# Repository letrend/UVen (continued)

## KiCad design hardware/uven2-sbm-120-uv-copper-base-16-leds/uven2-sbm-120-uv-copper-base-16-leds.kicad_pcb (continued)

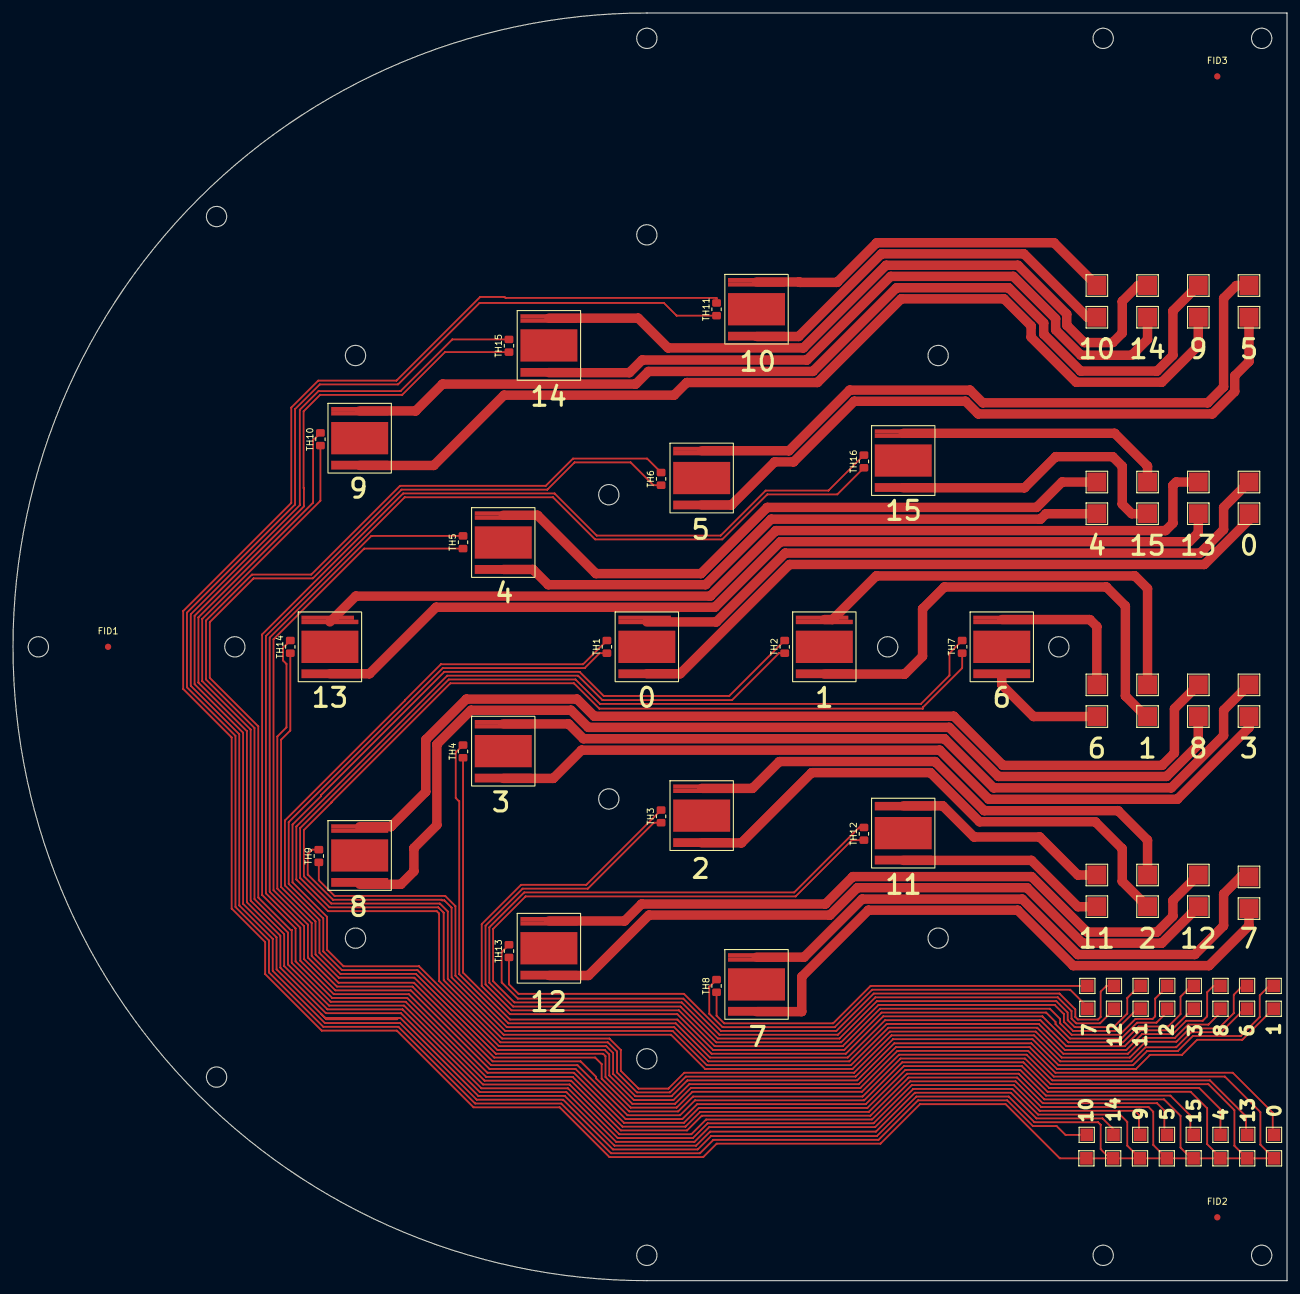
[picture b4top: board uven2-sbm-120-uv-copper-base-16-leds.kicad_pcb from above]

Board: 2 copper layers, 201.0 x 200.0 mm, 119 parts (0 on the bottom side), 49 nets.

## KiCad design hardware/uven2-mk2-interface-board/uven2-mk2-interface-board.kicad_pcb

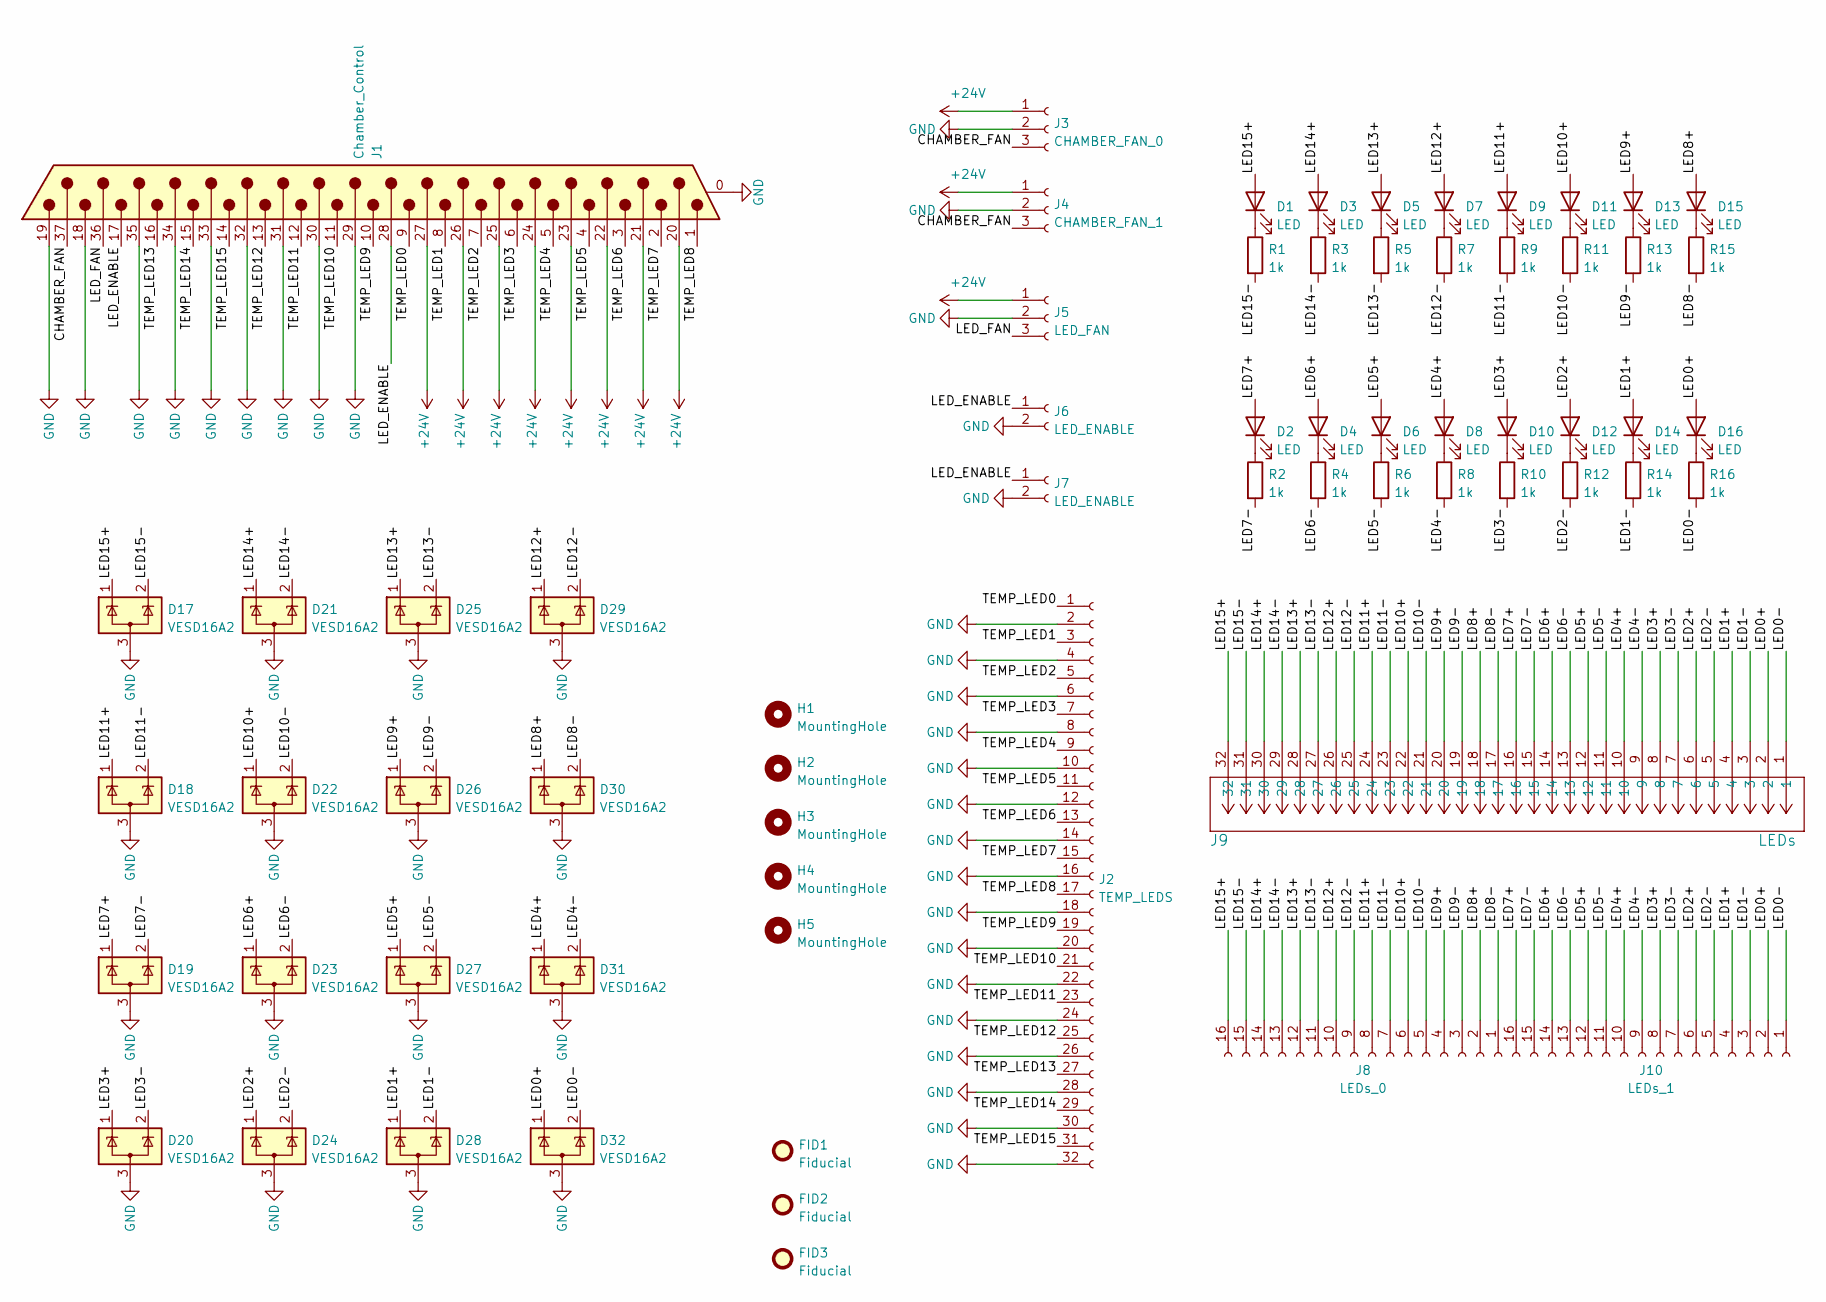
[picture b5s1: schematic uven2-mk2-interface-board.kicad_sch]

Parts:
D1, D2, D3, D4, D5, D6, D7, D8, D9, D10, D11, D12, D13, D14, D15, D16: LED; LED_0805_2012Metric_Pad1.15x1.40mm_HandSolder
D17, D18, D19, D20, D21, D22, D23, D24, D25, D26, D27, D28, D29, D30, D31, D32: VESD16A2; SOT-23
FID1, FID2, FID3: Fiducial; Fiducial_1mm_Dia_2.54mm_Outer_CopperTop
H1, H2, H3, H4, H5: MountingHole; MountingHole_3.2mm_M3
J1: Chamber_Control; DSUB-37_Female_Horizontal_P2.77x2.84mm_EdgePinOffset7.70mm_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
J2: TEMP_LEDS; PinHeader_2x16_P2.54mm_Vertical
J3: CHAMBER_FAN_0; PinHeader_1x03_P2.54mm_Vertical
J4: CHAMBER_FAN_1; PinHeader_1x03_P2.54mm_Vertical
J5: LED_FAN; PinHeader_1x03_P2.54mm_Vertical
J6, J7: LED_ENABLE; PinHeader_1x02_P2.54mm_Vertical
J8: LEDs_0; PinHeader_1x16_P2.54mm_Vertical
J9: LEDs; CONN_713-1436&slash_037-000_WAG
J10: LEDs_1; PinHeader_1x16_P2.54mm_Vertical
R1, R2, R3, R4, R5, R6, R7, R8, R9, R10, R11, R12, R13, R14, R15, R16: 1k; R_0603_1608Metric_Pad0.98x0.95mm_HandSolder

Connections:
+24V: J1.20, J1.21, J1.22, J1.23, J1.24, J1.25, J1.26, J1.27, J3.1, J4.1, J5.1
/CHAMBER_FAN: J1.37, J3.3, J4.3
/LED0+: D16.2 (A), D32.1 (K), J9.2, J10.2
/LED0-: D32.2 (K), J9.1, J10.1, R16.2
/LED1+: D14.2 (A), D28.1 (K), J9.4, J10.4
/LED1-: D28.2 (K), J9.3, J10.3, R14.2
/LED2+: D12.2 (A), D24.1 (K), J9.6, J10.6
/LED2-: D24.2 (K), J9.5, J10.5, R12.2
/LED3+: D10.2 (A), D20.1 (K), J9.8, J10.8
/LED3-: D20.2 (K), J9.7, J10.7, R10.2
/LED4+: D8.2 (A), D31.1 (K), J9.10, J10.10
/LED4-: D31.2 (K), J9.9, J10.9, R8.2
/LED5+: D6.2 (A), D27.1 (K), J9.12, J10.12
/LED5-: D27.2 (K), J9.11, J10.11, R6.2
/LED6+: D4.2 (A), D23.1 (K), J9.14, J10.14
/LED6-: D23.2 (K), J9.13, J10.13, R4.2
/LED7+: D2.2 (A), D19.1 (K), J9.16, J10.16
/LED7-: D19.2 (K), J9.15, J10.15, R2.2
/LED8+: D15.2 (A), D30.1 (K), J8.2, J9.18
/LED8-: D30.2 (K), J8.1, J9.17, R15.2
/LED9+: D13.2 (A), D26.1 (K), J8.4, J9.20
/LED9-: D26.2 (K), J8.3, J9.19, R13.2
/LED10+: D11.2 (A), D22.1 (K), J8.6, J9.22
/LED10-: D22.2 (K), J8.5, J9.21, R11.2
/LED11+: D9.2 (A), D18.1 (K), J8.8, J9.24
/LED11-: D18.2 (K), J8.7, J9.23, R9.2
/LED12+: D7.2 (A), D29.1 (K), J8.10, J9.26
/LED12-: D29.2 (K), J8.9, J9.25, R7.2
/LED13+: D5.2 (A), D25.1 (K), J8.12, J9.28
/LED13-: D25.2 (K), J8.11, J9.27, R5.2
/LED14+: D3.2 (A), D21.1 (K), J8.14, J9.30
/LED14-: D21.2 (K), J8.13, J9.29, R3.2
/LED15+: D1.2 (A), D17.1 (K), J8.16, J9.32
/LED15-: D17.2 (K), J8.15, J9.31, R1.2
/LED_ENABLE: J1.17, J1.28, J6.1, J7.1
/LED_FAN: J1.36, J5.3
/TEMP_LED0: J1.9, J2.1
/TEMP_LED1: J1.8, J2.3
/TEMP_LED2: J1.7, J2.5
/TEMP_LED3: J1.6, J2.7
/TEMP_LED4: J1.5, J2.9
/TEMP_LED5: J1.4, J2.11
/TEMP_LED6: J1.3, J2.13
/TEMP_LED7: J1.2, J2.15
/TEMP_LED8: J1.1, J2.17
/TEMP_LED9: J1.10, J2.19
/TEMP_LED10: J1.11, J2.21
/TEMP_LED11: J1.12, J2.23
/TEMP_LED12: J1.13, J2.25
/TEMP_LED13: J1.16, J2.27
/TEMP_LED14: J1.15, J2.29
/TEMP_LED15: J1.14, J2.31
GND: D17.3 (A), D18.3 (A), D19.3 (A), D20.3 (A), D21.3 (A), D22.3 (A), D23.3 (A), D24.3 (A), D25.3 (A), D26.3 (A), D27.3 (A), D28.3 (A), D29.3 (A), D30.3 (A), D31.3 (A), D32.3 (A), J1.0 (PAD), J1.18, J1.19, J1.29, J1.30, J1.31, J1.32, J1.33, J1.34, J1.35, J2.2, J2.4, J2.6, J2.8, J2.10, J2.12, J2.14, J2.16, J2.18, J2.20, J2.22, J2.24, J2.26, J2.28, J2.30, J2.32, J3.2, J4.2, J5.2, J6.2, J7.2
unnamed: D1.1 (K), R1.1
unnamed: D2.1 (K), R2.1
unnamed: D3.1 (K), R3.1
unnamed: D4.1 (K), R4.1
unnamed: D5.1 (K), R5.1
unnamed: D6.1 (K), R6.1
unnamed: D7.1 (K), R7.1
unnamed: D8.1 (K), R8.1
unnamed: D9.1 (K), R9.1
unnamed: D10.1 (K), R10.1
unnamed: D11.1 (K), R11.1
unnamed: D12.1 (K), R12.1
unnamed: D13.1 (K), R13.1
unnamed: D14.1 (K), R14.1
unnamed: D15.1 (K), R15.1
unnamed: D16.1 (K), R16.1

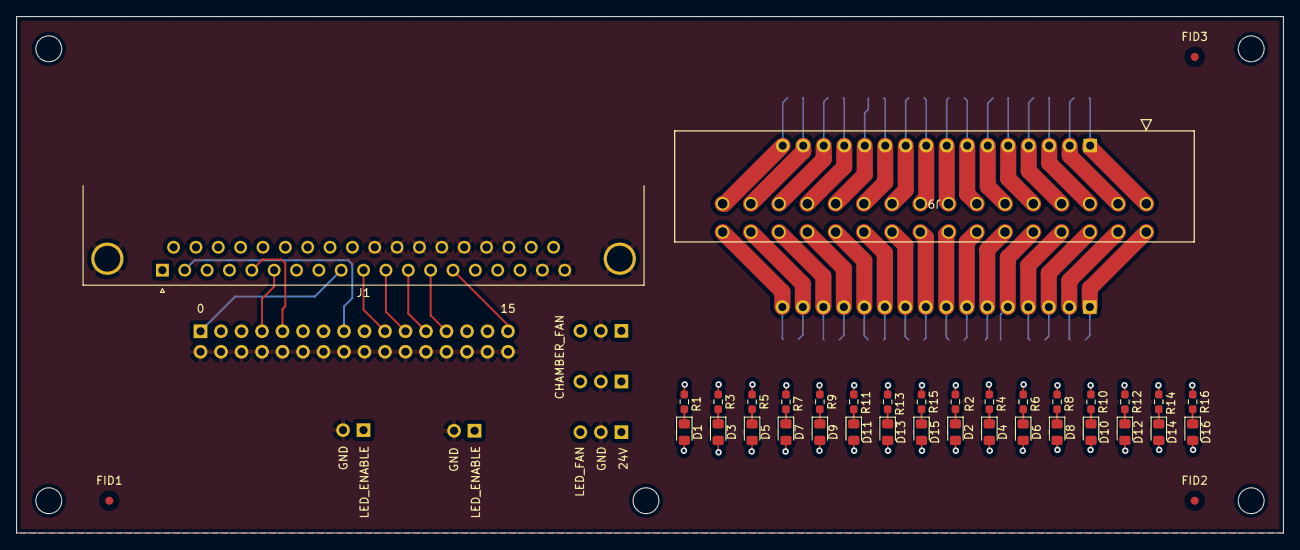
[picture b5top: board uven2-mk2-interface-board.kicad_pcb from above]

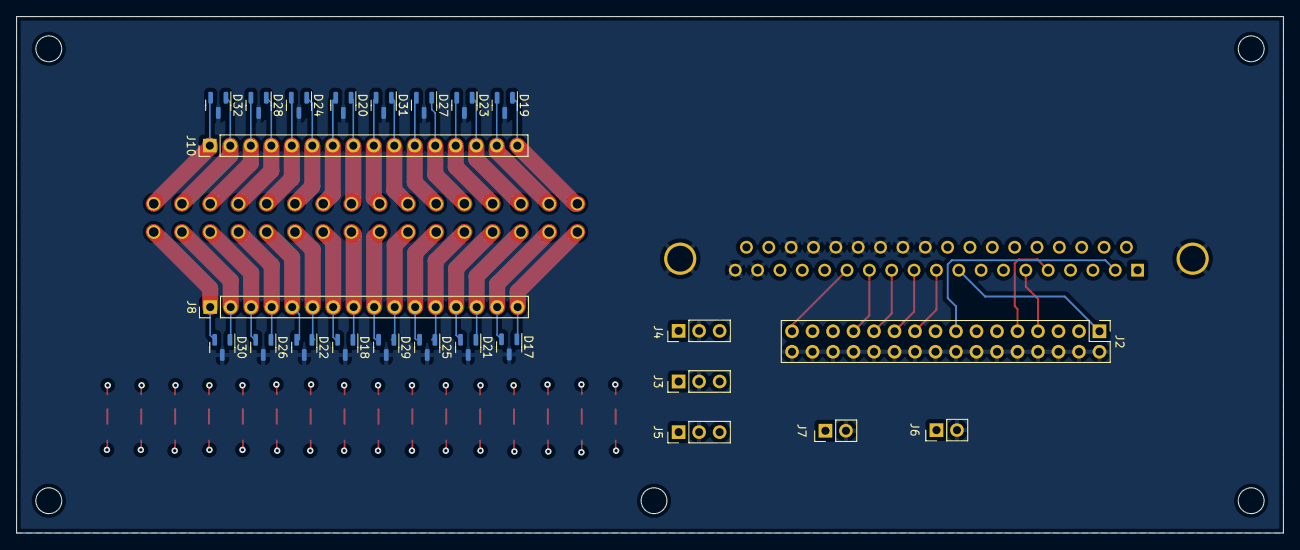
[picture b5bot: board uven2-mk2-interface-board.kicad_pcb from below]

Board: 4 copper layers, 157.0 x 64.0 mm, 66 parts (24 on the bottom side), 69 nets.

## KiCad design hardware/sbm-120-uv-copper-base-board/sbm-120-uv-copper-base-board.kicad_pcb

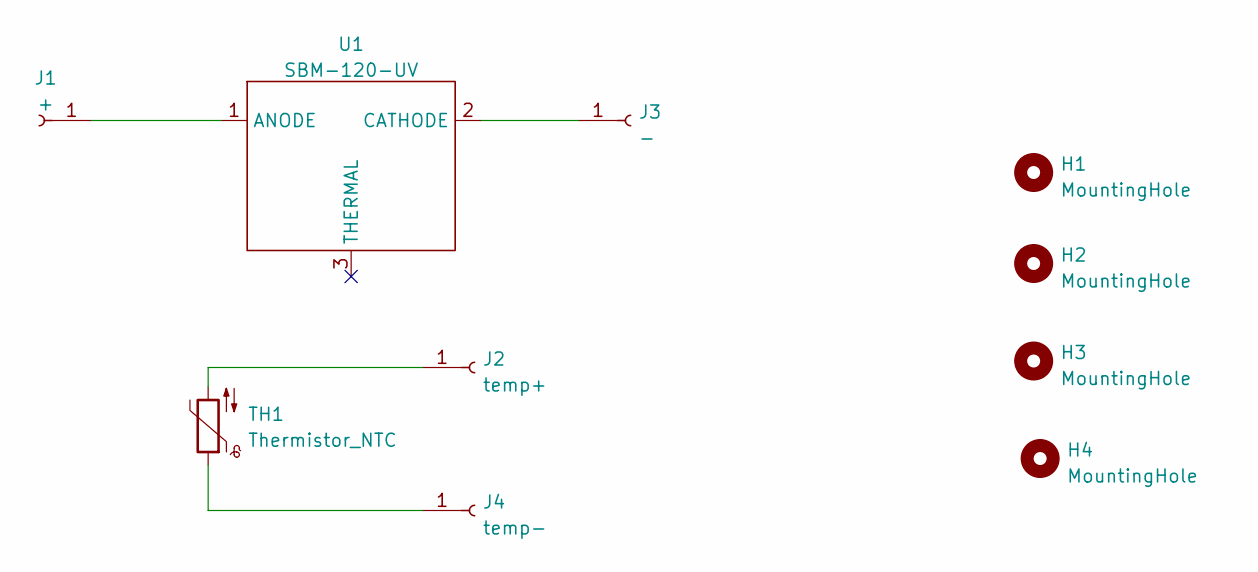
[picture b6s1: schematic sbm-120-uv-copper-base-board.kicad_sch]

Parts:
H1, H2, H3, H4: MountingHole; MountingHole_3.2mm_M3
J1: +; TestPoint_Pad_3.0x3.0mm
J2: temp+; TestPoint_Pad_1.5x1.5mm
J3: -; TestPoint_Pad_3.0x3.0mm
J4: temp-; TestPoint_Pad_1.5x1.5mm
TH1: Thermistor_NTC; R_0805_2012Metric_Pad1.20x1.40mm_HandSolder
U1: SBM-120-UV

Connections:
unnamed: J1.1, U1.1 (ANODE)
unnamed: J3.1, U1.2 (CATHODE)
unnamed: J4.1, TH1.1
unnamed: J2.1, TH1.2

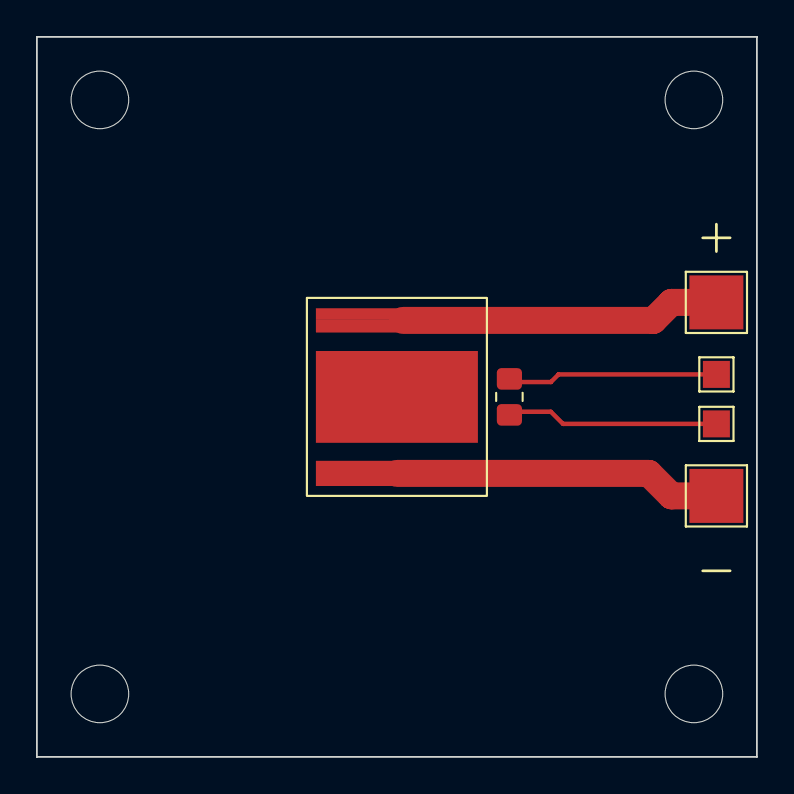
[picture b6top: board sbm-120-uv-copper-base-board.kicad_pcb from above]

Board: 2 copper layers, 40.0 x 40.0 mm, 10 parts (0 on the bottom side), 4 nets.

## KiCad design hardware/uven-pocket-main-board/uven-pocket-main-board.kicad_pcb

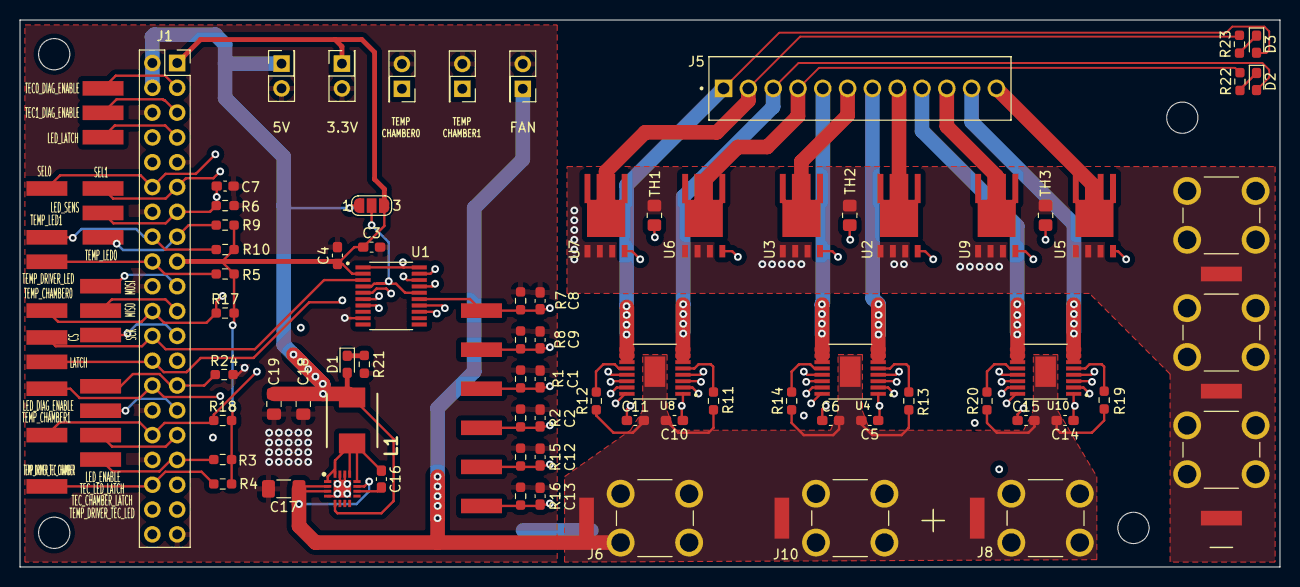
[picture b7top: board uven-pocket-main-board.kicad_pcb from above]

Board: 4 copper layers, 129.0 x 56.0 mm, 113 parts (0 on the bottom side), 57 nets.

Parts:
11111: TS30012-M050QFNR; QFN50P300X300X100-17N-D
C1, C2, C3, C8, C9, C12, C13: 100n; C_0603_1608Metric_Pad1.08x0.95mm_HandSolder
C4: 10uF; C_0603_1608Metric_Pad1.08x0.95mm_HandSolder
C5, C10, C14: 220n; C_0603_1608Metric_Pad1.08x0.95mm_HandSolder
C6, C11, C15: 4.7u; C_0603_1608Metric_Pad1.08x0.95mm_HandSolder
C7: 10n; C_0603_1608Metric_Pad1.08x0.95mm_HandSolder
C16: 0.022uF 10V; C_0603_1608Metric_Pad1.08x0.95mm_HandSolder
C17: 10uF 35V; C_1206_3216Metric_Pad1.33x1.80mm_HandSolder
C18, C19: 22uF; C_0805_2012Metric_Pad1.18x1.45mm_HandSolder
D1, D2, D3: LED; LED_0603_1608Metric_Pad1.05x0.95mm_HandSolder
H1, H2, H3, H4: MountingHole; MountingHole_3.2mm_M3
J1: Raspberry_Pi_2_3; PinSocket_2x20_P2.54mm_Vertical
J2: FAN; PinSocket_2x01_P2.54mm_Vertical
J3: TEMP_CHAMBER1; PinSocket_2x01_P2.54mm_Vertical
J4: TEMP_CHAMBER0; PinSocket_2x01_P2.54mm_Vertical
J5: 1-282834-2; TE_1-282834-2
J6, J8, J10: VDrive; KEYSTONE_7767
J7, J9, J11: GND; KEYSTONE_7767
J12: 3.3V; PinSocket_2x01_P2.54mm_Vertical
J13: 5V; PinSocket_2x01_P2.54mm_Vertical
JP1: Vref_select; SolderJumper-3_P1.3mm_Open_RoundedPad1.0x1.5mm_NumberLabels
L1: IHLP2020CZER4R7MA1; INDPM5552X300N
R1, R2, R6, R7, R8, R15, R16: 1k; R_0603_1608Metric_Pad0.98x0.95mm_HandSolder
R3, R4, R5, R9, R10, R11, R12, R13, R14, R17, R18, R19, R20, R22, R23, R24: 10k; R_0603_1608Metric_Pad0.98x0.95mm_HandSolder
R21: 1K; R_0603_1608Metric_Pad0.98x0.95mm_HandSolder
TH1, TH2, TH3: Thermistor_NTC; R_0805_2012Metric_Pad1.20x1.40mm_HandSolder
TP1: GATE_LED0; TP420X150
TP2: GATE_LED1; TP420X150
TP3: GATE_TEC0; TP420X150
TP4: GATE_TEC1; TP420X150
TP5: GATE_TEC2; TP420X150
TP6: GATE_TEC3; TP420X150
TP7, TP9, TP11: VDrive; TP420X150
TP8, TP10, TP12: GND; TP420X150
TP13: TEMP_DRIVER_LED; TP420X150
TP14: TEMP_CHAMBER0; TP420X150
TP15: LED_SENS; TP420X150
TP16: TEMP_DRIVER_TEC_CHAMBER; TP420X150
TP17: TEMP_LED0; TP420X150
TP18: TEMP_LED1; TP420X150
TP19: SEL1; TP420X150
TP20: SEL0; TP420X150
TP21: LATCH; TP420X150
TP22: CS; TP420X150
TP23: MISO; TP420X150
TP24: MOSI; TP420X150
TP25: SCK; TP420X150
TP26: LED_ENABLE; TP420X150
TP27: LED_DIAG_ENABLE; TP420X150
TP28: TEC0_DIAG_ENABLE; TP420X150
TP29: TEC1_DIAG_ENABLE; TP420X150
TP30: LED_LATCH; TP420X150
TP31: TEC_LED_LATCH; TP420X150
TP32: TEC_CHAMBER_LATCH; TP420X150
TP33: TEMP_CHAMBER1; TP420X150
TP34: TEMP_DRIVER_TEC_LED; TP420X150
U1: MCP48FEB28T-20E/ST; SOP65P640X120-20N
U2, U3, U5, U6, U7, U9: SIDR392DP-T1-GE3; PowerPAK SO-8DC
U4, U8, U10: TPS2HB50BQPWPRQ1; SOP65P640X120-17N

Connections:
+3.3V: C3.1, C4.1, J1.1 (3V3), J1.17 (3V3), J12.1, JP1.3 (B), R3.2, R4.2, R5.2, R9.2, R10.2, R17.2, R18.2, U1.2 (VDD)
+5V: 11111.5 (FB), C18.2, C19.2, D1.2 (A), J1.2 (5V), J1.4 (5V), J13.1, JP1.1 (A), L1.2
/CS: J1.24 (~CE0/GPIO8), TP22.1, U1.3 (CS)
/GATE_LED0: C9.2, R8.2, TP1.1, U1.5 (VOUTO), U6.4 (G)
/GATE_LED1: C8.2, R7.2, TP2.1, U1.15 (VOUT1), U7.4 (G)
/GATE_TEC0: C2.2, R2.2, TP3.1, U1.6 (VOUT2), U2.4 (G)
/GATE_TEC1: C1.2, R1.2, TP4.1, U1.14 (VOUT3), U3.4 (G)
/GATE_TEC2: C13.2, R16.2, TP5.1, U1.7 (VOUT4), U5.4 (G)
/GATE_TEC3: C12.2, R15.2, TP6.1, U1.13 (VOUT5), U9.4 (G)
/LATCH: J1.26 (~CE1/GPIO7), TP21.1, U1.1 (LAT1), U1.20 (LAT0)
/LED0+: D2.2 (A), J5.3, U8.6 (VOUT1), U8.7 (VOUT1), U8.8 (VOUT1)
/LED0-: J5.4, R22.2, U6.5 (D)
/LED1+: D3.2 (A), J5.1, U8.9 (VOUT2), U8.10 (VOUT2), U8.11 (VOUT2)
/LED1-: J5.2, R23.2, U7.5 (D)
/LED_DIAG_ENABLE: J1.28 (ID_SC/GPIO1), TP27.1, U8.16 (DIA_EN)
/LED_ENABLE: J1.27 (ID_SD/GPIO0), R24.2, TP26.1, U8.4 (EN1), U8.13 (EN2)
/LED_LATCH: J1.7 (GCLK0/GPIO4), TP30.1, U8.3 (LATCH)
/LED_SENS: C7.1, J1.13 (GPIO27), R6.1, TP15.1, U4.2 (SNS), U8.2 (SNS), U10.2 (SNS)
/SEL0: J1.12 (GPIO18/PWM0), TP20.1, U4.14 (SEL1), U8.14 (SEL1), U10.14 (SEL1)
/SEL1: J1.11 (GPIO17), TP19.1, U4.15 (SEL2), U8.15 (SEL2), U10.15 (SEL2)
/SPI_MISO: J1.21 (MISO0/GPIO9), TP23.1, U1.17 (SDO)
/SPI_MOSI: J1.19 (MOSI0/GPIO10), TP24.1, U1.19 (SDI)
/SPI_SCK: J1.23 (SCLK0/GPIO11), TP25.1, U1.18 (SCK)
/TEC0+: J5.7, U4.6 (VOUT1), U4.7 (VOUT1), U4.8 (VOUT1)
/TEC0-: J5.8, U2.5 (D)
/TEC0_DIAG_ENABLE: J1.3 (SDA/GPIO2), TP28.1, U4.16 (DIA_EN)
/TEC1+: J5.5, U4.9 (VOUT2), U4.10 (VOUT2), U4.11 (VOUT2)
/TEC1-: J5.6, U3.5 (D)
/TEC1_DIAG_ENABLE: J1.5 (SCL/GPIO3), TP29.1, U10.16 (DIA_EN)
/TEC2+: J5.11, U10.6 (VOUT1), U10.7 (VOUT1), U10.8 (VOUT1)
/TEC2-: J5.12, U5.5 (D)
/TEC3+: J5.9, U10.9 (VOUT2), U10.10 (VOUT2), U10.11 (VOUT2)
/TEC3-: J5.10, U9.5 (D)
/TEC_CHAMBER_LATCH: J1.31 (GCLK2/GPIO6), TP32.1, U10.3 (LATCH)
/TEC_ENABLE: U4.4 (EN1), U4.13 (EN2), U10.4 (EN1), U10.13 (EN2)
/TEC_LED_LATCH: J1.29 (GCLK1/GPIO5), TP31.1, U4.3 (LATCH)
/TEMP_CHAMBER0: J1.22 (GPIO25), J4.1, R17.1, TP14.1
/TEMP_CHAMBER1: J1.32 (PWM0/GPIO12), J3.1, R18.1, TP33.1
/TEMP_DRIVER_LED: J1.18 (GPIO24), R5.1, TH1.2, TP13.1
/TEMP_DRIVER_TEC_CHAMBER: J1.36 (GPIO16), R4.1, TH3.2, TP16.1
/TEMP_DRIVER_TEC_LED: J1.33 (PWM1/GPIO13), R3.1, TH2.2, TP34.1
/TEMP_LED0: J1.15 (GPIO22), R9.1, TP17.1
/TEMP_LED1: J1.16 (GPIO23), R10.1, TP18.1
GND: 11111.4 (GND), 11111.14 (PGND_1), 11111.15 (PGND_2), 11111.17 (EP), C1.1, C2.1, C3.2, C4.2, C5.1, C6.1, C7.2, C8.1, C9.1, C10.1, C11.1, C12.1, C13.1, C14.1, C15.1, C17.2, C18.1, C19.1, J1.6 (GND), J1.9 (GND), J1.14 (GND), J1.20 (GND), J1.25 (GND), J1.30 (GND), J1.34 (GND), J1.39 (GND), J2.2, J3.2, J4.2, J7.1, J7.2, J7.3, J7.4, J9.1, J9.2, J9.3, J9.4, J11.1, J11.2, J11.3, J11.4, J12.2, J13.2, R1.1, R2.1, R6.2, R7.1, R8.1, R15.1, R16.1, R21.2, R24.1, TH1.1, TH2.1, TH3.1, TP8.1, TP10.1, TP12.1, U1.9 (VSS), U2.1 (S), U2.2 (S), U2.3 (S), U3.1 (S), U3.2 (S), U3.3 (S), U4.1 (GND), U5.1 (S), U5.2 (S), U5.3 (S), U6.1 (S), U6.2 (S), U6.3 (S), U7.1 (S), U7.2 (S), U7.3 (S), U8.1 (GND), U9.1 (S), U9.2 (S), U9.3 (S), U10.1 (GND)
unnamed: 11111.1 (VSW_1), 11111.12 (VSW_2), 11111.13 (VSW_3), 11111.16 (VSW_4), C16.1, L1.1
unnamed: 11111.10 (BST), C16.2
unnamed: D1.1 (K), R21.1
unnamed: D2.1 (K), R22.1
unnamed: D3.1 (K), R23.1
unnamed: JP1.2 (C), U1.4 (VREF0), U1.16 (VREF1)
unnamed: R11.2, U8.5 (ILIM1)
unnamed: R12.2, U8.12 (ILIM2)
unnamed: R13.2, U4.5 (ILIM1)
unnamed: R14.2, U4.12 (ILIM2)
unnamed: R19.2, U10.5 (ILIM1)
unnamed: R20.2, U10.12 (ILIM2)
Vdrive: 11111.2 (VCC_1), 11111.3 (VCC_2), 11111.11 (VCC_3), C5.2, C6.2, C10.2, C11.2, C14.2, C15.2, C17.1, J2.1, J6.1, J6.2, J6.3, J6.4, J8.1, J8.2, J8.3, J8.4, J10.1, J10.2, J10.3, J10.4, R11.1, R12.1, R13.1, R14.1, R19.1, R20.1, TP7.1, TP9.1, TP11.1, U4.17 (VBB), U8.17 (VBB), U10.17 (VBB)

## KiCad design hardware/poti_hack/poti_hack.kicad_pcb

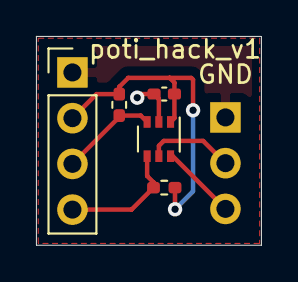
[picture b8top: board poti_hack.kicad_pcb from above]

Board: 2 copper layers, 12.5 x 11.6 mm, 6 parts (1 on the bottom side), 6 nets.

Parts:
C1: 100nF; C_0402_1005Metric_Pad0.74x0.62mm_HandSolder
J1: POTI_i2c; PinHeader_1x04_P2.54mm_Vertical
J2: POTI; PinHeader_1x03_P2.54mm_Vertical
R1, R2: 10k; R_0402_1005Metric_Pad0.72x0.64mm_HandSolder
U1: MCP4018-xxxxLT; SOT-363_SC-70-6

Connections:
+3V3: C1.1, J1.2, R1.1, R2.1, U1.1
GND: C1.2, J1.1, J2.1, U1.2
unnamed: J1.3, R2.2, U1.3
unnamed: J1.4, R1.2, U1.4
unnamed: J2.2, U1.5
unnamed: J2.3, U1.6

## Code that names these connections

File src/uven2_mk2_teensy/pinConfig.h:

#define LATCH0 6
#define LATCH1 7
#define CS0 37
#define CS1 36
#define LED_ENABLE 2
#define LED_SENS A0
#define TEMP_LED0 A1
#define TEMP_LED1 A2
#define TEMP_LED2 A3
#define TEMP_LED3 A4
#define TEMP_LED4 A5
#define TEMP_LED5 A6
#define TEMP_LED6 A7
#define TEMP_LED7 A8
#define TEMP_LED8 A9
#define TEMP_LED9 A10
#define TEMP_LED10 A11
#define TEMP_LED11 A12
#define TEMP_LED12 A13
#define TEMP_LED13 A14
#define TEMP_LED14 A15
#define TEMP_LED15 A16
#define TEMP_DRIVER A17
#define LED_SEL0 4
#define LED_SEL1 5
#define LED_DIAG_ENABLE_A 8
#define LED_DIAG_ENABLE_B 9
#define LED_DIAG_ENABLE_C 35
#define LED_DIAG_ENABLE_D 32
#define LED_DIAG_ENABLE_E 30
#define LED_DIAG_ENABLE_F 31
#define LED_DIAG_ENABLE_G 33
#define LED_DIAG_ENABLE_H 34
#define LED_LATCH 3
#define LED_FAN 28
#define CHAMBER_FAN 29

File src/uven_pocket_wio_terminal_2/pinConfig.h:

#define LED_ENABLE BCM0
#define LED_DIAG_ENABLE BCM1
#define TEC0_DIAG_ENABLE BCM2
#define TEC1_DIAG_ENABLE BCM3
#define LED_LATCH BCM4
#define TEC_LED_LATCH BCM5
#define TEC_CHAMBER_LATCH BCM6
#define LATCH BCM7
#define CS BCM8
#define SPI_MISO BCM9
#define SPI_MOSI BCM10
#define SPI_SCK BCM11
#define TEMP_CHAMBER1 BCM12
#define TEMP_DRIVER_TEC_LED BCM13
#define TEMP_DRIVER_TEC_CHAMBER BCM16
#define SEL1 BCM17
#define SEL0 BCM18
#define TEMP_LED0 BCM22
#define TEMP_LED1 BCM23
#define TEMP_DRIVER_LED BCM24
#define TEMP_CHAMBER0 BCM25
#define LED_SENS BCM27

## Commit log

2021-03-04 with mounting holes, ready to order
2021-03-04 better
2021-03-15 smaller and square
2021-03-16 draft main board
2021-03-16 more layout
2021-03-16 almoscht done
2021-03-16 with buttons
2021-03-19 done and ordered
2021-03-25 raw readout draft:
2021-04-08 with thermistor calibration values
2021-04-08 with polynomial fit for thermistor
2021-04-16 draft
2021-04-16 with funky qwt dials
2021-04-16 with button dim control
2021-04-18 with over current/temp and trigger function
2021-04-18 with neopixel
2021-04-22 with higher current limit
2021-04-25 with lid safety check
2021-04-25 show error type
2021-05-02 with launch file
2021-05-04 with jhigerh threshold
2021-05-08 that should do it
2021-05-09 v1 ordered on aisler
2021-05-29 poti hack ros controlled
2021-06-03 double dabble motherfucker
2021-06-04 with i2c
2021-06-08 save 100 value
2021-06-10 encoder button menu
2021-06-20 oh yeah
2021-06-22 done
2021-08-01 with endless loop option
2021-08-01 better timeout
2021-08-02 fix lid bug
2021-08-03 fixed timeout
2021-11-20 relay ativation, then intensity handled by i2c control
2021-11-24 shorter default pulses
2021-11-28 debounce encoder
2021-12-28 parabol fit
2021-12-28 schematics for one current controller
2021-12-29 course layout done
2021-12-30 layout almost done
2021-12-30 layout done
2021-12-30 ready for order
2021-12-31 with step export
2022-01-01 with correct fpc connector and pullup on enable
2022-01-01 with 3d model fpc connector
2022-05-08 better deafutls and menu navigation
2022-11-07 with draft uven 2d
2022-11-12 with symbol
2022-11-12 pcb ordered in aisler
2022-11-27 with temp calibration
2023-01-28 step
2023-01-29 led control draft
2023-01-29 temp control draft
2023-01-29 bang bang tec controller
2023-03-15 with tft display working and showing temperature
2023-03-18 menu setpoints
2023-04-05 spi slave draft for arduino due
2023-04-07 copper base board draft
2023-04-07 communication working
2023-04-07 proper frames between wio and due
2023-04-07 with crc checksum
2023-04-07 with actual uven pocket control
2023-04-07 control field filled with status from pocket
2023-04-07 plotting all three temperatures
2023-04-07 with crc mismatch notification
2023-04-08 with coms reset via pin
2023-04-08 with setpoints
2023-04-08 with communication recovery by resetting arduino due
2023-04-08 gui almost finished
2023-04-15 ray tracing draft
2023-04-16 raytracing works
2023-04-21 more stable coms
2023-04-22 much more stable coms
2023-04-23 cuda version
2023-04-23 cuda quaternion draft
2023-04-24 cuda quaternion implementation seems to be working, but the ray generation is weird
2023-04-24 with better absolut angle for intensity
2023-04-24 bigger step length
2023-04-24 with actual uven2 led positions
2023-04-24 with bigger screen for visualizing lost light
2023-04-24 squeezing the python
2023-04-24 massiv parallelgit statusgit status
2023-04-24 final render
2023-04-29 more mounting holes
2023-04-29 draft uven2 mk2 mainboard
2023-04-30 with current limiting switch
2023-04-30 with wago connector
2023-04-30 firmware 'functional'
2023-05-02 slower coms seems to solve the communication issues
2023-05-02 still no stable coms...:(
2023-05-07 also doesn't fix coms
2023-05-08 with bom
2023-05-08 more parts
2023-05-09 with different mosfet
2023-05-10 with chamber control
2023-05-11 schematics done
2023-05-15 layout led driver almost done
2023-05-15 layout almost finished
2023-05-16 layout finished
2023-05-16 with thermistors
2023-05-16 interface board done
2023-05-20 uven pocket layout almost finished
2023-05-21 single led copper base + uven pocket finished
2023-06-03 dac control draft
2023-06-05 with current sens control loop
2023-06-06 calibration uvenpocket thermistor
2023-06-08 with step
2023-06-08 freertos started
2023-06-08 ramp up to avoid over current latch
2023-06-08 with tec soft ramp up
2023-06-09 two leds closed loop
2023-06-10 tec control
2023-06-17 better current control and tec enable pins for relays
2023-06-17 with display control
2023-06-17 with tex indicator and emergency off release
2023-06-17 with separate button for emergency off and release
2023-07-08 ordered on jlcpcb
2023-07-29 serial control test
2023-07-30 serial coms working between teensy and wio
2023-07-31 with control fromm wio
2023-08-06 steps
2023-08-11 with tcp working
2023-08-12 with tcp teensy
2023-08-12 with mk2 functionalities
2023-08-12 full range fan
2023-08-12 with current calibration
2023-08-14 current contro global
2023-08-15 external temp readout
2023-08-15 with temp calbration
2023-08-15 fixed current conversion, crash of gui on disconnect
2023-08-15 full power test, unlatch leds on interock event
2023-08-15 with gui slicer gui for wio termial
2023-08-16 gui looks good
2023-08-16 menu control working
2023-08-20 each led current tuned
2023-08-23 with display coms working
2023-08-23 full control via display
2023-08-25 more aggressive current controller, overtemp, scale led fan wrt led temp max
2023-08-26 with ethernet overriding display control
2023-08-27 with chamber fan control
2023-08-28 gitignores
2023-08-28 timer also ready
2023-08-29 fine tuned
2023-08-29 plotting data
2023-08-30 with user manual
2023-09-01 with timer showing correctly and adjusted current limits
2023-09-16 the strange offsets seem to stem from an empty multimeter, measuring gargabe...:D
2023-09-16 with 4000mA current range
2023-09-17 power supply seems to be maxed out >3.5A, limiting current
2023-09-20 with dipslay control for uven pocket
2023-09-28 100% default 1min default
2024-04-27 uven only
2024-04-27 fixed 3.3V trace missing, added footage
2025-03-28 cc schematics
2025-03-28 cc driver test draft
2025-03-29 ordered
2025-04-13 with combined pdf for assembly
2025-04-13 fix mosfet wrong orientation
2025-05-26 easyeda single led driver
2025-05-28 with 80x driver draft
2025-05-29 20x driver
2025-06-08 connectors for interface board
2025-06-11 using gnd
2025-06-18 using simpler driver ic
2025-06-18 more schematcis
2025-06-19 finished layout
2025-06-30 100x led array draft
2025-06-30 fanout led
2025-07-05 3d model
2025-07-06 25x driver draft
2025-07-06 with mounting holes
2025-07-06 using avail connectors
2025-07-06 with step file
2025-07-13 connectors 0.26mm further out
2025-07-13 layout started
2025-08-17 with interlock switches
2025-08-19 with fan control
2025-08-25 with all prices
2025-09-05 shortened right side by 0.25mm to fit the housing
2025-09-06 with direct heat sink pad
2025-09-09 with name and version number on the PCB
2025-09-10 with direct heat sink pad min width >=1mm as per jlcpcb requirmenet
2025-09-24 main board control draft
2025-10-24 more ui
2025-10-24 looks pretty good
2025-10-24 works
2025-11-02 with repetitions
2025-11-02 with saving and loading ui state to sdcard
2025-11-02 small bugs
2025-11-02 with timer delay compensation
2025-11-02 removed files from other versions
2025-11-02 with github links
2025-11-02 with hackaday links to step files
2025-11-03 fix polarity inversion on edge connector, fix ctrl logic
2025-11-03 fix bugs on main board
2025-11-23 added direct heat sink pad of leds
2025-11-29 assembly instructions draft
2025-11-30 more steps
2025-11-30 all mechanical assembly steps
2025-11-30 added missing chamber_front drawing
2025-12-05 with zemax ray simulation
2025-12-05 no center
2025-12-05 with absolut irradiance in W/cm^2 extracted from datasheet
2025-12-17 fixed wrong relay type, diode polarity
2025-12-17 fix time overflow in display
2025-12-20 single led absoult power simulation
2025-12-20 2.5A
2025-12-20 simulated all
2025-12-20 simulated
2025-12-26 relay for each fan line, interlock ports for each switch
2025-12-31 3d export
2025-12-31 with wiring
2025-12-31 bom ods and most recent drawing
2026-01-07 much bigger time selectable, 3 state reps
2026-01-07 3 rep state, touch and hold time selection, rep once
2026-01-07 correct pin for second relay
2026-01-16 with bom and placement files
2026-01-16 updated 12V fan to stronger version, alternative link to fischer cooler
2026-01-19 with decisencond timers, max time 999.9 seconds, time counting up if repetitions was selected
2026-01-20 PA8 is used for controlling the LED fan
2026-03-12 increased track distance to 0.17mm for 2oz copper manufacture requirement
2026-03-12 extended copper poors a bit
